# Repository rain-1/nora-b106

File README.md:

# NORA-B106 board workspace

**Latest design: [Dragon P3.2](square-p3/README.md), 40.5 × 49.5 mm, twelve GPIOs,
SWD and a centred optional USB-C socket.** This rectangular update keeps
1.6 mm thickness and fits within a 50 × 50 mm tier. It has an optional reset
button, four M2 holes, a white cyber dragon and the Codex / Backplane
credit. Minimum assembly remains the module and two capacitors.
Use its [current Gerber ZIP](square-p3/fabrication/nora-dragon-P3_2-gerbers.zip),
[ordering/pinout guide](square-p3/hardware/README.md) and
[small-stencil guidance](square-p3/hardware/STENCIL.md).
It keeps P1's exact electrical pinout and uses the existing P1 USB firmware;
see the [programming guide](square-p3/programming/README.md) and
[dragon preview](square-p3/preview/back-artwork.png).
CAD and static firmware compatibility checks pass; hardware remains untested.
Run `make -C square-p3 fabrication` for validation and exports.

**Latest compact design: [Compact P2](minimal-p2/README.md), 31.5 × 27.5 mm,
four GPIOs, SWD and optional through-hole USB-A.** This uses 35% less PCB area
than Minimal P1, with the same minimum assembly of the module and two capacitors.
Use its [Gerber ZIP](minimal-p2/fabrication/nora-minimal-P2-gerbers.zip),
[pinout/ordering guide](minimal-p2/hardware/README.md) and
[matching built USB firmware](minimal-p2/firmware/README.md).
Its six-pin GPIO header differs from both earlier designs. The USB bootloader
needs an initial SWD installation. CAD and firmware checks pass; hardware is
physically untested. Run `make -C minimal-p2 fabrication` for its validation and
exports. Earlier projects below are retained separately.

Revision D is a 36 x 36 mm two-layer NORA-B106 breakout for self assembly.
It exposes SWD, twelve GPIOs, optional USB-C power/data, an LED, and reset.

- [Assembly options, pinouts, and JLCPCB settings](hardware/README.md)
- [Pico programmer wiring and first tests](programming/README.md)
- [Parts list with SWD-only / USB population choices](hardware/BOM.csv)
- [Bare-PCB Gerber ZIP](fabrication/nora-b106-breakout-revD-gerbers.zip)
- [Assembly drawing](fabrication/preview/assembly-top.png)
- [Schematic preview](fabrication/preview/nora-b106-board.png)

CAD validation passed with zero ERC, DRC, unconnected-item, or schematic-parity
issues. The hardware and programmer connection have not been physically tested.
Revision D groups all twelve GPIOs plus 3V3/GND on a single 14-pin header
along the right edge, with SWD on the left. J3 has a new pinout; see the wiring
guide. The module ground-plane improvements are retained. Use the revision D Gerbers; earlier
revisions are retained in Git history. Debian 13's packaged OpenOCD is too old for the Pico route;
the programming guide provides a newer source build and an offline check.
For the lowest part count, start with the SWD-only population and power it from
a Pico's 3V3 OUT, following the wiring guide. The USB population uses its own
regulator; do not connect Pico 3V3 in that configuration.

## Minimal P1: new Backplane-designed board and USB firmware

[Minimal P1](minimal-p1/README.md) is a separate 36.5 × 36.5 mm design with a
minimum SWD population of the module and two capacitors, twelve unloaded GPIOs,
and an optional through-hole USB-A plug. Its **1.6 mm thickness and J3 pinout
are different from revision D**. All ordering, pinout and firmware instructions
for it are under `minimal-p1/`; do not mix its files with revision D.

The P1 project opens in KiCad 9. Built MCUboot USB recovery and USB serial
GPIO/ADC test firmware, including an initial SWD factory image and subsequent
USB update image, are in [minimal-p1/firmware](minimal-p1/firmware/README.md).
The USB bootloader must first be installed via SWD. CAD checks, firmware builds
and static checks pass; neither board nor USB/SWD has been physically tested.

```
make -C minimal-p1 check
make -C minimal-p1 firmware-setup
make -C minimal-p1 firmware
```

## Install on this machine

This workspace targets Debian 13's KiCad 9 packages. Run in your terminal:

```sh
sudo apt update
sudo apt install kicad kicad-symbols kicad-footprints kicad-templates
make doctor
```

The `kicad` package includes the GUI applications, `kicad-cli`, and the Python
`pcbnew` board API. Use `/usr/bin/python3` for board scripts so Debian's Python
modules are available. Optional 3D component models can be installed with
`sudo apt install kicad-packages3d`.

## Project workflow

Open `nora-b106-board.kicad_pro` in KiCad 9 to review the schematic and routed PCB. Keep `.kicad_pro`, `.kicad_sch`,
`.kicad_pcb`, custom symbols, custom footprints, and library tables together.
Reference project libraries through `${KIPRJMOD}` so they remain portable.

```sh
make doctor          # Verify the installed tools and libraries
make ipc-status      # Inspect the PCB currently open in the editor
make check           # Schematic ERC and board DRC; violations fail the command
make preview         # Schematic and PCB layer SVGs for inspection
```

Reports go into `build/reports/` and SVGs into `build/preview/`. These generated
files and KiCad's local UI state are ignored by Git. The Git repository is
hosted at https://github.com/rain-1/nora-b106.

The default filenames are `nora-b106-board.kicad_sch` and
`nora-b106-board.kicad_pcb`. Override them when necessary:

```sh
make check SCHEMATIC=hardware/main.kicad_sch BOARD=hardware/main.kicad_pcb
```

I can edit native project files, use Python for PCB changes, inspect exports,
and run checks through the CLI. For direct file edits, close the relevant editor
first and reopen afterward so unsaved GUI state does not overwrite changes.
Electrical connectivity, footprint pin mappings, RF layout, and manufacturing
constraints still need review against the component datasheets; ERC and DRC
alone do not establish that a design is correct.

## Live PCB connection and agent skill

The official IPC API is enabled in this machine's KiCad 9 preferences. The
previous configuration is backed up at
`~/.config/kicad/9.0/kicad_common.json.before-live-api`. Missing standard symbol
and footprint library tables were initialized from KiCad's bundled tables.

The local `.venv` contains `kicad-python==0.4.0`, tested against the installed
KiCad 9.0.2. Its API definitions report version 9.0.3 and its compatibility check
passes. Newer API methods may still require a newer KiCad release. To recreate
this environment:

```sh
uv venv --python /usr/bin/python3 --system-site-packages .venv
uv pip install --python .venv/bin/python -r requirements-kicad.txt
```

Open the intended PCB in KiCad, then run `make ipc-status`. This reads the board
path, footprints, and item counts without changing the design. For a specific
board or socket:

```sh
.venv/bin/python tools/kicad_ipc.py --board /path/to/board.kicad_pcb
.venv/bin/python tools/kicad_ipc.py --socket /tmp/kicad/api.sock
```

Live edit scripts can import `connect_board` from `tools.kicad_ipc`. Supply the
expected board path before editing; the helper rejects a different open file.
Multiple sockets require an explicit choice. Use the board's commit API for
undoable changes and save before running file-based exports or checks. KiCad 9
IPC supports the PCB editor, not the schematic editor. Modal dialogs can block
API requests; close them before retrying.

The project skill lives at `.agents/skills/nora-kicad/SKILL.md` and is linked
into this machine's Codex skills directory. It can be invoked as `$nora-kicad`
and is scoped to work in this workspace. No third-party MCP server is needed.

Integration was verified on the disposable board under
`build/integration-smoke/`: API discovery, board-path checks, staged edit
rollback, an undoable footprint move, saving, independent file reload, DRC,
and SVG exports. This board is a tooling test, not the NORA-B106 design.

Command reference: [KiCad 9 CLI documentation](https://docs.kicad.org/9.0/en/cli/cli.html).

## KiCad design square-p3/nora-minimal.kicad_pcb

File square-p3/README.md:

# NORA-B106 Dragon P3.2 — USB-C

**40.5 × 49.5 mm**, two layers, **1.6 mm FR4**. The USB-C socket is centred
on the bottom edge and all **four M2 mounting holes** are present. This is
slightly wider than P3.1 to keep the top mounting hardware clear of the antenna,
and still fits within a 50 × 50 mm size tier. The directory name `square-p3/`
is retained; these are the current P3.2 files.

Minimum assembly remains **U1 + C1 (4.7 µF) + C2 (100 nF)**. Headers, USB and
SW1 are optional. Power the SWD-only build from regulated 3.3 V. The optional
6 mm through-hole reset button makes USB recovery convenient without an extra
reset wire. It adds no required components.

- [Current USB-C Gerber ZIP](fabrication/nora-dragon-P3_2-gerbers.zip)
- [Assembly, pinouts and order settings](hardware/README.md)
- [Front assembly drawing](preview/assembly.png)
- [Dragon on the back](preview/back-artwork.png) and [native silk preview](preview/back-labels.svg)
- [Schematic](preview/nora-minimal.svg)
- [Top paste stencil Gerber](fabrication/gerbers/nora-minimal-F_Paste.gtp)
- [Small frameless stencil options](hardware/STENCIL.md)
- [Pico/SWD and USB installation](programming/README.md)
- [Flash the next minimum board with the Pico](programming/NEXT_BOARD.md)
- [Signed Bluetooth application updates](firmware/ble-ota/README.md)
- [BOM](hardware/BOM.csv) and [validation](verification.md)

USB uses the **HRO TYPE-C-31-M-12** sixteen-contact USB 2.0 receptacle. Its
contacts are SMD and its four shell anchors are through-hole. CC1 and CC2 each
have their own **5.1 kΩ, 1%, 0805** pull-down resistor. Both D+ contacts are
joined, and both D− contacts are joined, supporting either cable orientation.
SBU1/SBU2 remain unconnected. This is a 5 V USB device: no USB-PD controller,
higher-voltage negotiation, USB host or USB 3 data function is implemented.
Use a data-capable A-to-C or C-to-C cable to a computer for programming/console.

The module, twelve GPIOs, power isolation jumper, protection device and reset
button retain the P1-compatible electrical interfaces. Use the unchanged
[built P1 USB firmware](../minimal-p1/firmware/README.md); USB product names
still say NORA Minimal P1. Install the bootloader through SWD first. Press and
release SW1 to enter USB recovery after that installation. P2 and revision D
have different GPIO headers; use this project's pinout guide.

The native KiCad 9 PCB is authoritative. Module/SWD/GPIO routing was retained;
the connector area was rerouted. The antenna keepout, six antenna-end grounds,
continuous back ground beneath U1, local 100 nF capacitor and 0.4 mm main power
routes are retained. The white back-silkscreen cyber dragon and Codex/Backplane
credit add no decorative copper or solder-mask openings. [Artwork](artwork/README.md)
includes the original generated source, cleaned vectors and prompt.

Open `nora-minimal.kicad_pro` with its local libraries. Run `make check`,
`make fabrication` or `make firmware-check` here. Checks include the USB-C pad
mapping, separate CC pull-downs, unchanged firmware-facing interfaces and shared
P1 artifact hashes, plus eight uploader tests. No firmware rebuild is required.

CAD/static checks pass. One minimum U1/C1/C2 assembly has now passed 3.3 V,
Pico 2 W SWD, external LED, standalone firmware and UART-console tests,
including a power cycle. Separate [Bluetooth bring-up firmware](firmware/ble/README.md)
has started its host/controller, and the user confirmed seeing
`NORA Dragon D25D` in a Bluetooth scanner. RF range/performance, USB and ADC
remain untested. See the
[physical bring-up record](programming/BRINGUP.md). Older P3/P3.1 files are in
Git history; current order files use **P3.2**. P1/P2/revision D remain separate.

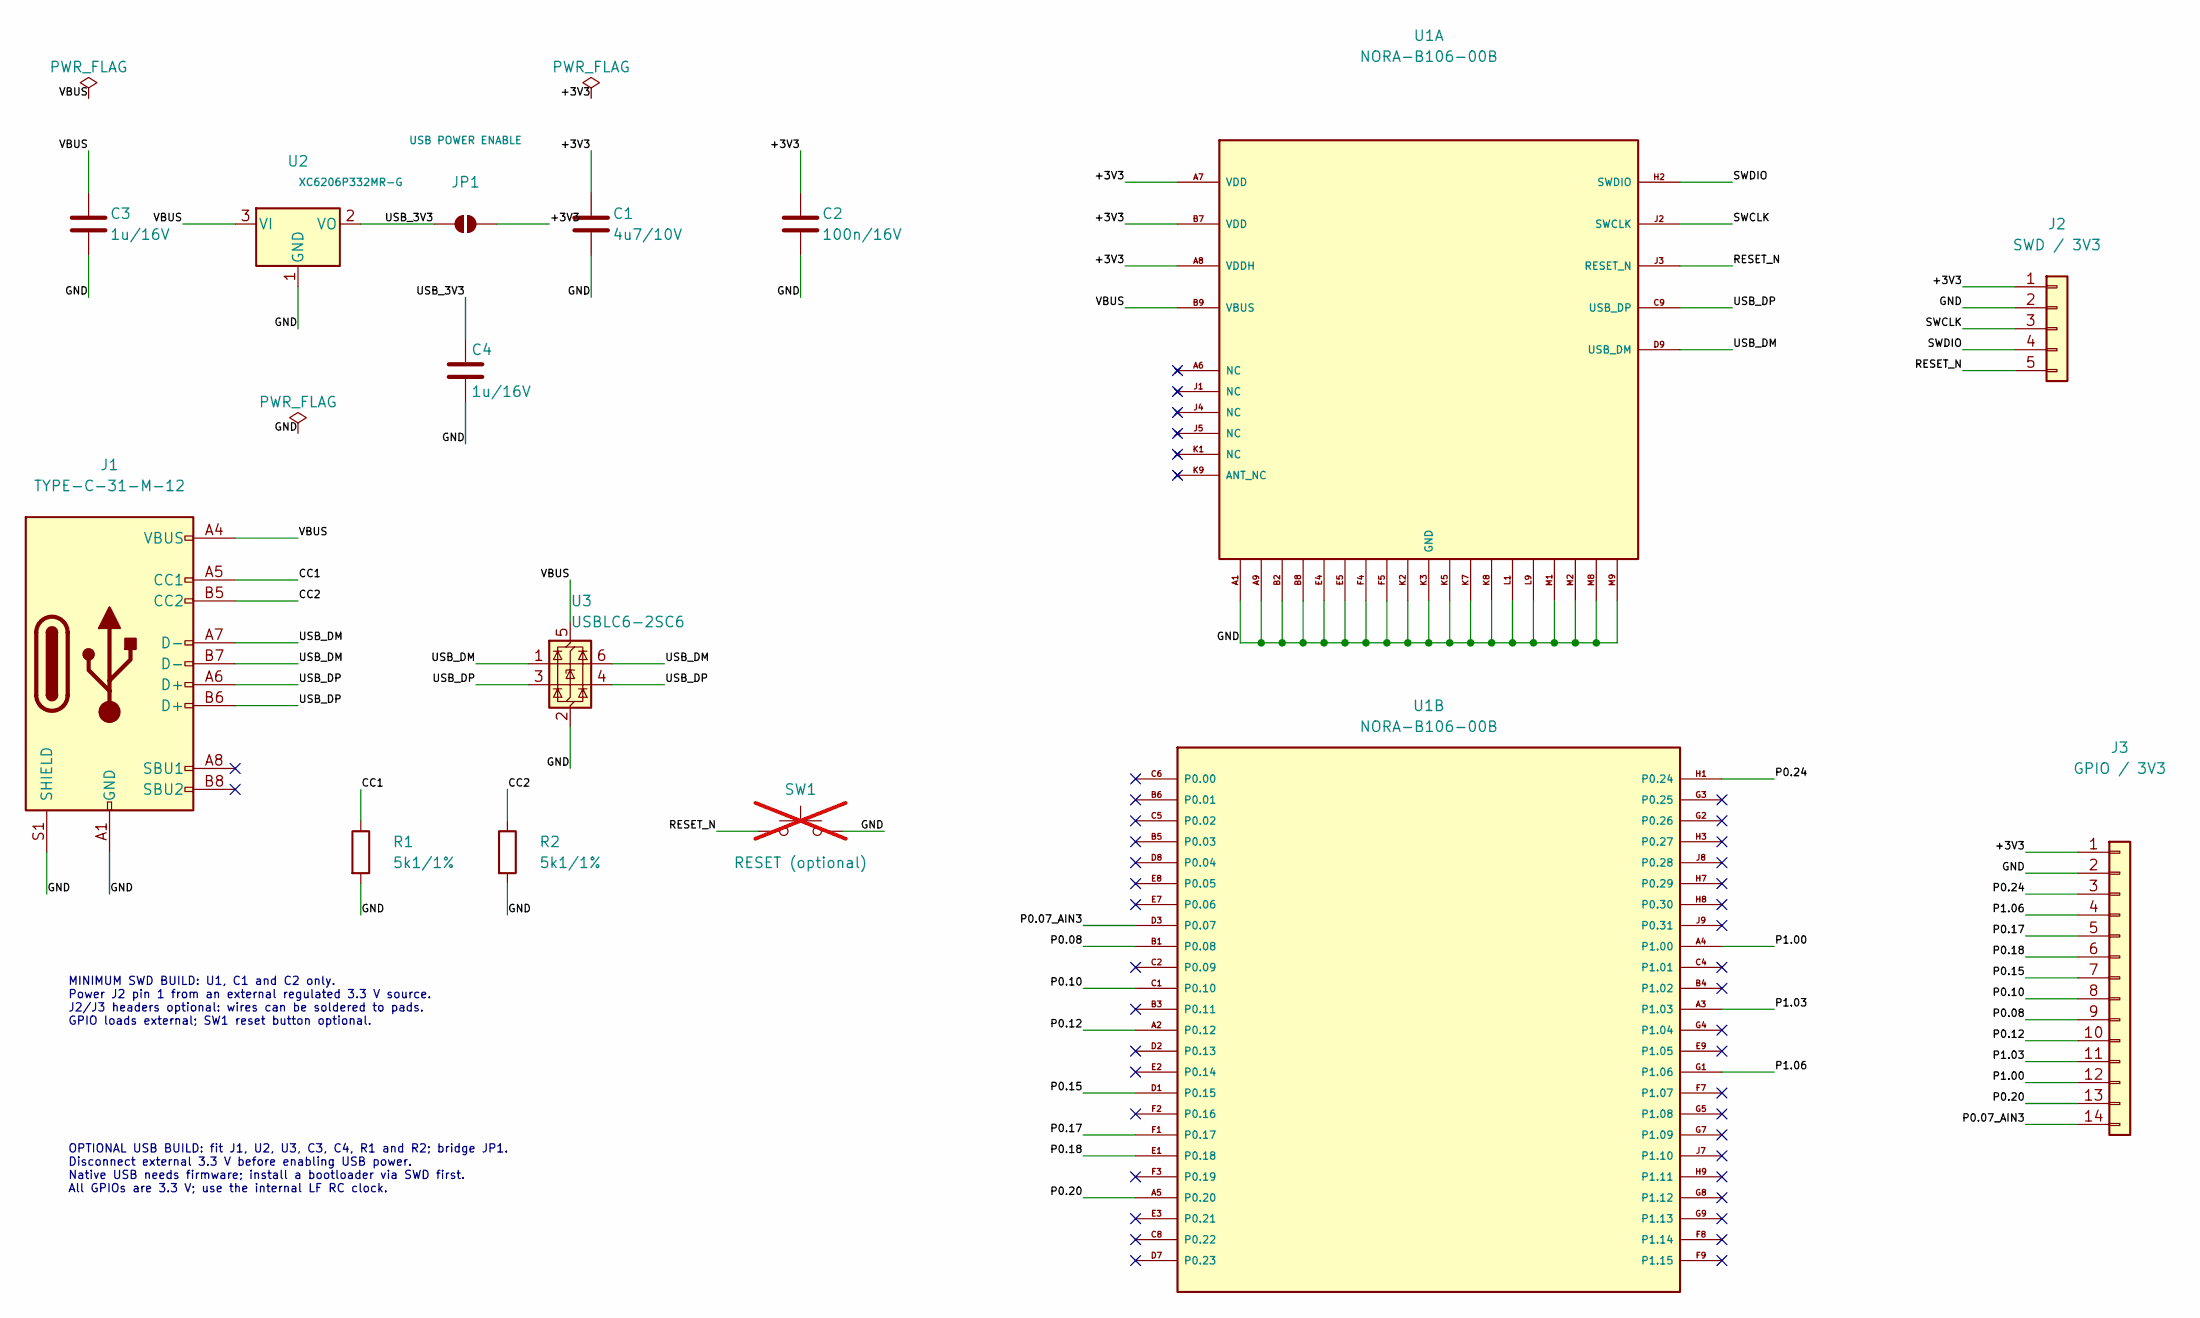
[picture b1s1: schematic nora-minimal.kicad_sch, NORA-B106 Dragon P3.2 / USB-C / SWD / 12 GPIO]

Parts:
C1: 4u7/10V; C_0805_2012Metric
C2: 100n/16V; C_0805_2012Metric
C3, C4: 1u/16V; C_0805_2012Metric
J1: TYPE-C-31-M-12; USB_C_Receptacle_HRO_TYPE-C-31-M-12
J2: SWD / 3V3; PinHeader_1x05_P2.54mm_Vertical
J3: GPIO / 3V3; PinHeader_1x14_P2.54mm_Vertical
JP1: USB POWER ENABLE; SolderJumper-2_P1.3mm_Open_RoundedPad1.0x1.5mm
R1, R2: 5k1/1%; R_0805_2012Metric
SW1: RESET (optional); SW_PUSH_6mm; not fitted
U1: NORA-B106-00B; NORA-B106
U2: XC6206P332MR-G; SOT-23-3
U3: USBLC6-2SC6; SOT-23-6

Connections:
/+3V3: C1.1, C2.1, J2.1, J3.1, JP1.2 (B), U1.A7 (VDD), U1.A8 (VDDH), U1.B7 (VDD)
/CC1: J1.A5 (CC1), R1.1
/CC2: J1.B5 (CC2), R2.1
/GND: C1.2, C2.2, C3.2, C4.2, J1.A1 (GND), J1.A12 (GND), J1.B1 (GND), J1.B12 (GND), J1.S1 (SHIELD), J2.2, J3.2, R1.2, R2.2, SW1.2, U1.A1, U1.A9, U1.B2, U1.B8, U1.E4, U1.E5, U1.F4, U1.F5, U1.K2, U1.K3 (GND), U1.K5, U1.K7, U1.K8, U1.L1, U1.L9, U1.M1, U1.M2, U1.M8, U1.M9, U2.1 (GND), U3.2 (GND)
/P0.07_AIN3: J3.14, U1.D3 (P0.07)
/P0.08: J3.9, U1.B1 (P0.08)
/P0.10: J3.8, U1.C1 (P0.10)
/P0.12: J3.10, U1.A2 (P0.12)
/P0.15: J3.7, U1.D1 (P0.15)
/P0.17: J3.5, U1.F1 (P0.17)
/P0.18: J3.6, U1.E1 (P0.18)
/P0.20: J3.13, U1.A5 (P0.20)
/P0.24: J3.3, U1.H1 (P0.24)
/P1.00: J3.12, U1.A4 (P1.00)
/P1.03: J3.11, U1.A3 (P1.03)
/P1.06: J3.4, U1.G1 (P1.06)
/RESET_N: J2.5, SW1.1, U1.J3 (RESET_N)
/SWCLK: J2.3, U1.J2 (SWCLK)
/SWDIO: J2.4, U1.H2 (SWDIO)
/USB_3V3: C4.1, JP1.1 (A), U2.2 (VO)
/USB_DM: J1.A7 (D-), J1.B7 (D-), U1.D9 (USB_DM), U3.1 (I/O1), U3.6 (I/O1)
/USB_DP: J1.A6 (D+), J1.B6 (D+), U1.C9 (USB_DP), U3.3 (I/O2), U3.4 (I/O2)
/VBUS: C3.1, J1.A4 (VBUS), J1.A9 (VBUS), J1.B4 (VBUS), J1.B9 (VBUS), U1.B9 (VBUS), U2.3 (VI), U3.5 (VBUS)

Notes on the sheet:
OPTIONAL USB BUILD: fit J1, U2, U3, C3, C4, R1 and R2; bridge JP1. Disconnect external 3.3 V before enabling USB power. Native USB needs firmware; install a bootloader via SWD first. All GPIOs are 3.3 V; use the internal LF RC clock.
MINIMUM SWD BUILD: U1, C1 and C2 only. Power J2 pin 1 from an external regulated 3.3 V source. J2/J3 headers optional: wires can be soldered to pads. GPIO loads external; SW1 reset button optional.

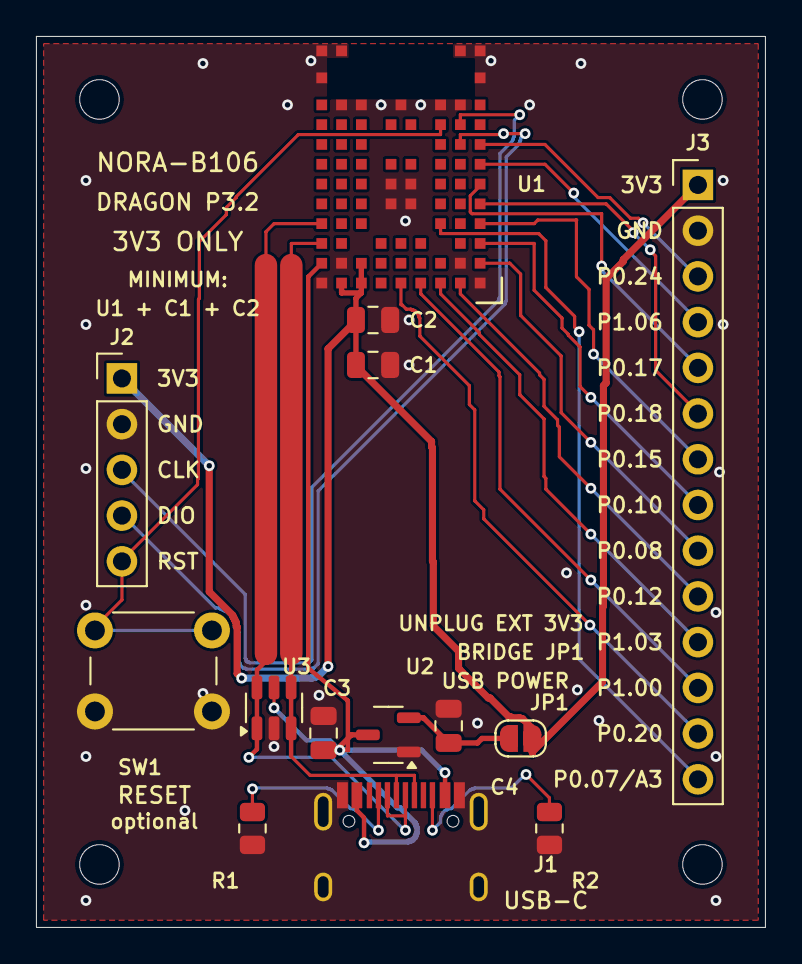
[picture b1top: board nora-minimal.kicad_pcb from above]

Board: 2 copper layers, 40.5 x 49.5 mm, 18 parts (0 on the bottom side), 23 nets.

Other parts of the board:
H1, H2, H3, H4: MountingHole_2.2mm_M2

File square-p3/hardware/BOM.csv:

Reference,Value / part,Package,Quantity,SWD-only,USB
U1,NORA-B106-00B,LGA82,1,required,required
C1,4.7uF 10V X7R,0805,1,required,required
C2,100nF 16V X7R,0805,1,required,required
J2,1x5 2.54mm header,THT,1,optional / wires,optional / wires
J3,1x14 2.54mm header,THT,1,optional / wires,optional / wires
J1,HRO TYPE-C-31-M-12 (LCSC C165948),USB-C SMD + through-hole shell,1,omit,required
U2,XC6206P332MR-G,SOT-23-3,1,omit,required
U3,USBLC6-2SC6,SOT-23-6,1,omit,required
C3 C4,1uF 16V X7R,0805,2,omit,required
JP1,Solder bridge,no purchased part,0,open,closed for USB power
SW1,RESET normally-open 6mm (optional),Breakout:SW_PUSH_6mm,1,optional,optional
R1,5.1k 1%,0805,1,omit,required
R2,5.1k 1%,0805,1,omit,required

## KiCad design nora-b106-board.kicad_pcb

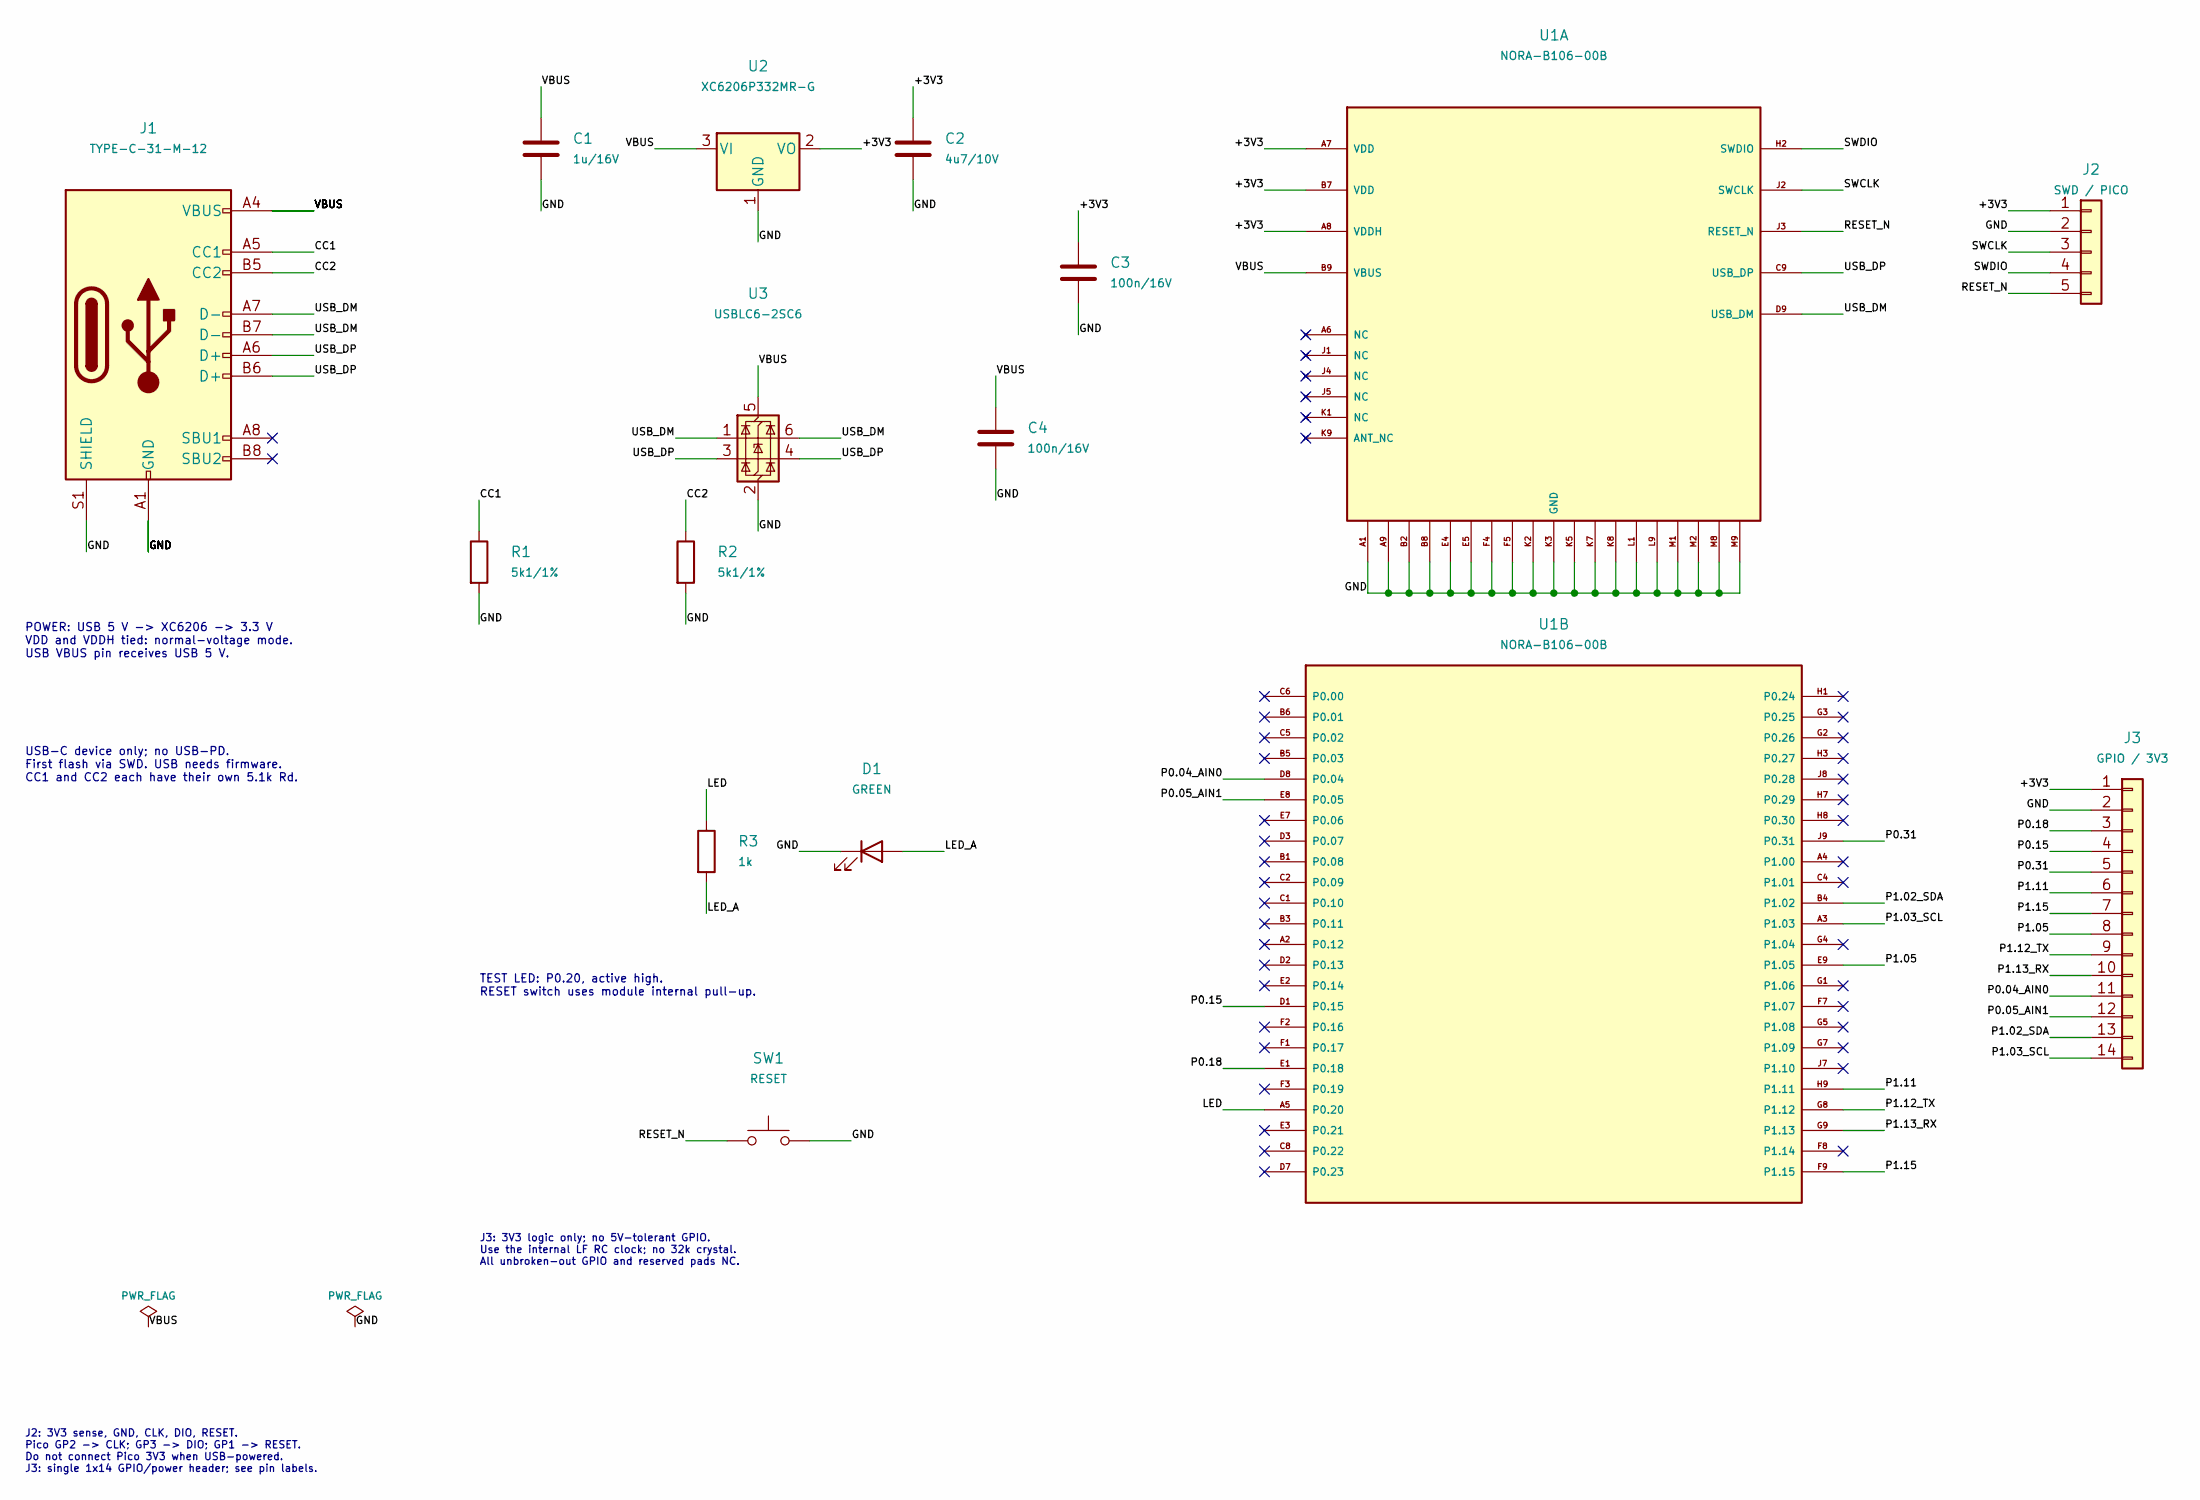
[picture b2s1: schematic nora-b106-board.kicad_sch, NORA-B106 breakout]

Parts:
C1: 1u/16V; C_0805_2012Metric
C2: 4u7/10V; C_0805_2012Metric
C3, C4: 100n/16V; C_0805_2012Metric
D1: GREEN; LED_0805_2012Metric
J1: TYPE-C-31-M-12; USB_C_Receptacle_HRO_TYPE-C-31-M-12
J2: SWD / PICO; PinHeader_1x05_P2.54mm_Vertical
J3: GPIO / 3V3; PinHeader_1x14_P2.54mm_Vertical
R1, R2: 5k1/1%; R_0805_2012Metric
R3: 1k; R_0805_2012Metric
SW1: RESET; SW_PUSH_6mm
U1: NORA-B106-00B; NORA-B106
U2: XC6206P332MR-G; SOT-23-3
U3: USBLC6-2SC6; SOT-23-6

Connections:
/+3V3: C2.1, C3.1, J2.1, J3.1, U1.A7 (VDD), U1.A8 (VDDH), U1.B7 (VDD), U2.2 (VO)
/CC1: J1.A5 (CC1), R1.1
/CC2: J1.B5 (CC2), R2.1
/GND: C1.2, C2.2, C3.2, C4.2, D1.1 (K), J1.A1 (GND), J1.A12 (GND), J1.B1 (GND), J1.B12 (GND), J1.S1 (SHIELD), J2.2, J3.2, R1.2, R2.2, SW1.2, U1.A1, U1.A9, U1.B2, U1.B8, U1.E4, U1.E5, U1.F4, U1.F5, U1.K2, U1.K3 (GND), U1.K5, U1.K7, U1.K8, U1.L1, U1.L9, U1.M1, U1.M2, U1.M8, U1.M9, U2.1 (GND), U3.2 (GND)
/LED: R3.1, U1.A5 (P0.20)
/LED_A: D1.2 (A), R3.2
/P0.04_AIN0: J3.11, U1.D8 (P0.04)
/P0.05_AIN1: J3.12, U1.E8 (P0.05)
/P0.15: J3.4, U1.D1 (P0.15)
/P0.18: J3.3, U1.E1 (P0.18)
/P0.31: J3.5, U1.J9 (P0.31)
/P1.02_SDA: J3.13, U1.B4 (P1.02)
/P1.03_SCL: J3.14, U1.A3 (P1.03)
/P1.05: J3.8, U1.E9 (P1.05)
/P1.11: J3.6, U1.H9 (P1.11)
/P1.12_TX: J3.9, U1.G8 (P1.12)
/P1.13_RX: J3.10, U1.G9 (P1.13)
/P1.15: J3.7, U1.F9 (P1.15)
/RESET_N: J2.5, SW1.1, U1.J3 (RESET_N)
/SWCLK: J2.3, U1.J2 (SWCLK)
/SWDIO: J2.4, U1.H2 (SWDIO)
/USB_DM: J1.A7 (D-), J1.B7 (D-), U1.D9 (USB_DM), U3.1 (I/O1), U3.6 (I/O1)
/USB_DP: J1.A6 (D+), J1.B6 (D+), U1.C9 (USB_DP), U3.3 (I/O2), U3.4 (I/O2)
/VBUS: C1.1, C4.1, J1.A4 (VBUS), J1.A9 (VBUS), J1.B4 (VBUS), J1.B9 (VBUS), U1.B9 (VBUS), U2.3 (VI), U3.5 (VBUS)

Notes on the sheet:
POWER: USB 5 V -> XC6206 -> 3.3 V VDD and VDDH tied: normal-voltage mode. USB VBUS pin receives USB 5 V.
USB-C device only; no USB-PD. First flash via SWD. USB needs firmware. CC1 and CC2 each have their own 5.1k Rd.
TEST LED: P0.20, active high. RESET switch uses module internal pull-up.
J2: 3V3 sense, GND, CLK, DIO, RESET. Pico GP2 -> CLK; GP3 -> DIO; GP1 -> RESET. Do not connect Pico 3V3 when USB-powered. J3: single 1x14 GPIO/power header; see pin labels.
J3: 3V3 logic only; no 5V-tolerant GPIO. Use the internal LF RC clock; no 32k crystal. All unbroken-out GPIO and reserved pads NC.

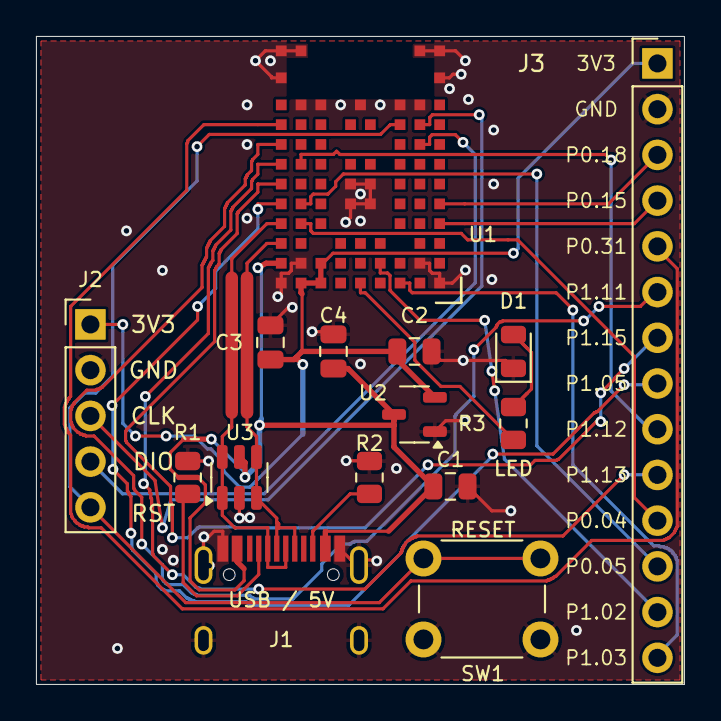
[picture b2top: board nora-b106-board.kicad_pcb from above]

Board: 2 copper layers, 36.0 x 36.0 mm, 15 parts (0 on the bottom side), 24 nets.

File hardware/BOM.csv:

Reference,Quantity,Value,Footprint,SWD-only build,USB build,Purchasing / assembly notes
U1,1,NORA-B106-00B,NORA-B106,Fit,Fit,"u-blox NORA-B106-00B, 82-pad LGA; antenna faces top board edge"
U2,1,XC6206P332MR-G,SOT-23-3,DNP,Fit,"Torex XC6206P332MR-G, SOT-23: 1 GND / 2 OUT / 3 IN"
U3,1,USBLC6-2SC6,SOT-23-6,DNP,Fit,"ST USBLC6-2SC6, SOT-23-6 (not USBLC6-2P6)"
J1,1,TYPE-C-31-M-12,USB_C_Receptacle_HRO_TYPE-C-31-M-12,DNP,Fit,"Exact HRO TYPE-C-31-M-12, not a generic USB-C connector"
J2,1,SWD / PICO,PinHeader_1x05_P2.54mm_Vertical,Fit,Fit,"1x5 2.54 mm straight pin header, or direct wires"
J3,1,GPIO / 3V3,PinHeader_1x14_P2.54mm_Vertical,Optional,Optional,"1x14 2.54 mm straight pin header, 2.54 mm-wide body; twelve GPIOs plus 3V3/GND"
R1,1,5k1/1%,R_0805_2012Metric,DNP,Fit,"5.1 kohm, 1%, 0805"
R2,1,5k1/1%,R_0805_2012Metric,DNP,Fit,"5.1 kohm, 1%, 0805"
R3,1,1k,R_0805_2012Metric,Optional,Optional,"1 kohm, 0805; fit with D1"
D1,1,GREEN,LED_0805_2012Metric,Optional,Optional,"Green 0805 LED; pad 1=cathode, pad 2=anode"
C1,1,1u/16V,C_0805_2012Metric,DNP,Fit,"1 uF, >=16 V, X7R, 0805"
C2,1,4u7/10V,C_0805_2012Metric,Fit,Fit,"4.7 uF, >=10 V, X7R, 0805"
C3,1,100n/16V,C_0805_2012Metric,Fit,Fit,"100 nF, >=16 V, X7R, 0805"
C4,1,100n/16V,C_0805_2012Metric,DNP,Fit,"100 nF, >=16 V, X7R, 0805"
SW1,1,RESET,SW_PUSH_6mm,Optional,Optional,"6 mm tactile, 6.5 x 4.5 mm pin spacing"
